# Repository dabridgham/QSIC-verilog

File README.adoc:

= QSIC - QBUS Storage and I/O Card

The QSIC is a QBUS card with an FPGA and SD cards that emulates the old DEC disk
controllers and drives.  A companion
http://github.com/dabridgham/Indicator-Panel[indicator panel] is also
available for those who want the blinkenlights.

This project has been split into separate repositories so that it
works better with git.  This repository primarily holds the Verilog
code that runs on the FPGAs.  It also holds the documentation and the
paper I wrote on bus arbitration.  Finally, just because there's no
more work being done on it, I've left the KiCad schematic for the
wire-wrapped prototype here as well.

So, directories you might care about are:

[horizontal]
board-wirewrap:: KiCad design for the wire-wrap prototype board
documentation:: Programming Manual for the QSIC/USIC
papers:: A paper on QBUS and Unibus arbitration
verilog:: The FPGA code to implement the QSIC

These directories, I'll probably make go away at some point but, for
now, I'll leave them be.

[horizontal]
board-prototype:: KiCad design for a prototype board with 8641 bus
		  transceivers (old idea)
board-qsic:: KiCad design for the QSIC hardware
board-smt:: KiCad design where I've been experimenting with discrete bus drivers
indicator-panel:: This directory is obsolete as the indicator panel has
		  been moved to its own project

Other QSIC-related repositories.

[horizontal]
https://github.com/dabridgham/QSIC[QSIC]:: The QSIC board
https://github.com/dabridgham/USIC[USIC]:: The USIC board
http://github.com/dabridgham/Indicator-Panel[Indicator Panel]:: Indicator Panel PCBs and graphics inlays
Software:: The software that runs on the embedded soft processor in
the QSIC/USIC (not yet started)

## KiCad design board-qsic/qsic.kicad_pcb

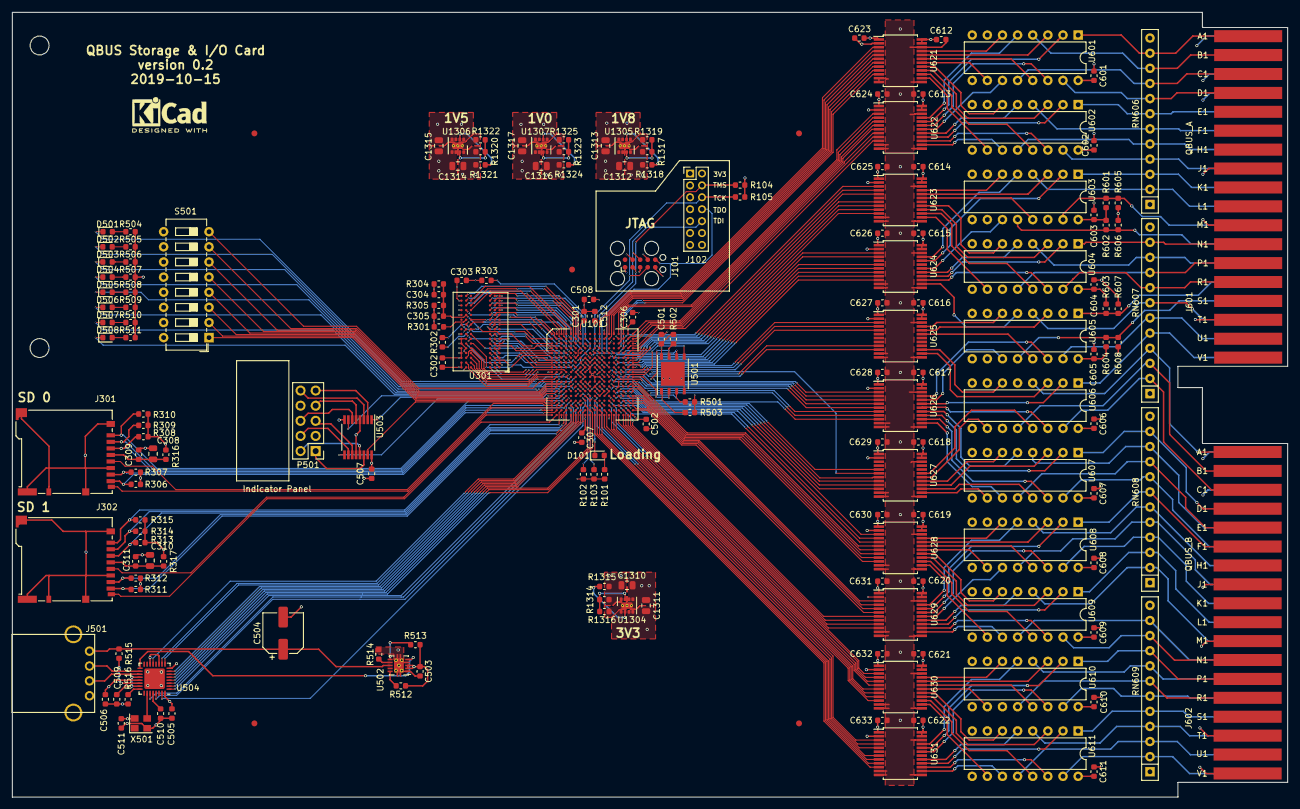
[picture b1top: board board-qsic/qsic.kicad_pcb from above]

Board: 4 copper layers, 214.1 x 131.7 mm, 183 parts (0 on the bottom side), 358 nets.

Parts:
C301, C306, C508, C512: 10µF; C_0603_1608Metric
C302, C303, C304, C305, C309, C311, C501, C503, C505, C506, C507, C601, C602, C603, C604, C605, C606, C607, C608, C609, C610, C611, C612, C613, C614, C615, C616, C617, C618, C619, C620, C621, C622, C623, C624, C625, C626, C627, C628, C629, C630, C631, C632, C633: 100nF; C_0603_1608Metric
C307, C502: 10uF; C_0603_1608Metric
C308, C310, C1310, C1312, C1314, C1316: 22µF; C_0805_2012Metric
C504: 150µF; CP_Elec_6.3x5.7
C509, C510: 1µF; C_0603_1608Metric
C511: 10nF; C_0603_1608Metric
C1311, C1313, C1315, C1317: 10µF; C_0805_2012Metric
D101, D501, D502, D503, D504, D505, D506, D507, D508: green; LED_0603_1608Metric
FID101, FID102, FID103, FID104, FID105: Fiducial; Fiducial_1mm_Mask2mm
J101: Conn_02x05_Odd_Even; Tag-Connect_TC2050-IDC-FP_2x05_P1.27mm_Vertical
J102: Conn_02x07_Odd_Even; PinHeader_2x07_P2.00mm_Vertical
J301: SD 0; microSD_HC_Hirose_DM3BT-DSF-PEJS
J302: SD 1; microSD_HC_Hirose_DM3BT-DSF-PEJS
J501: USB_A; USB-A-Amphenol-UE27
J601: QBUS_A; DEC_Edge_Fingers_single_height
J602: QBUS_B; DEC_Edge_Fingers_single_height
LOGO101: Logo_Open_Hardware_Small; KiCad-Logo2_5mm_SilkScreen
P501: Indicator Panel; Box_Header_2x05_P2.54mm
R101, R301, R504, R505, R506, R507, R508, R509, R510, R511: 240; R_0603_1608Metric
R102, R103, R501, R502: 4.7k; R_0603_1608Metric
R104, R105: 10k; R_0603_1608Metric
R302: 89; R_0603_1608Metric
R303: 47k; R_0603_1608Metric
R304, R305: 47 1%; R_0603_1608Metric
R306, R307, R308, R309, R310, R311, R312, R313, R314, R315: 50k; R_0603_1608Metric
R316, R317: 4.7; R_0603_1608Metric
R503: 2.4k; R_0603_1608Metric
R512, R513: 100k; R_0603_1608Metric
R514: 56.2k; R_0603_1608Metric
R515: 20k; R_0603_1608Metric
R516: 8.06k; R_0603_1608Metric
R601, R602, R603, R604: 330; R_0603_1608Metric
R605, R606, R607, R608: 680; R_0603_1608Metric
R1314: 511k; R_0603_1608Metric
R1315, R1318, R1321, R1324: 499k; R_0603_1608Metric
R1316, R1319, R1322, R1325: 162k; R_0603_1608Metric
R1317: 200k; R_0603_1608Metric
R1320: 143k; R_0603_1608Metric
R1323: 40.2; R_0603_1608Metric
RN606, RN607, RN608, RN609: 330/680; R_Array_SIP12
S501: Config; SW_DIP_SPSTx08_Slide_6.7x21.88mm_W7.62mm_P2.54mm_LowProfile
U101: XC7A75T-CSG324; BGA-324_15.0x15.0mm_Layout18x18_P0.8mm_Ball0.5mm_Pad0.4mm_N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
U301: IS43TR16128B; BGA-96_9.0x13.0mm_Layout2x3x16_P0.8mm
U501: MT25Q-mlq8; DFN-8-1EP_6x5mm_P1.27mm_EP4x4mm
U502: TPS2561; VSON-10-1EP_3x3mm_P0.5mm_EP1.65x2.4mm_ThermalVias
U503: MAX3033E; TSSOP-16_4.4x5mm_P0.65mm
U504: USB3340; QFN-32-1EP_5x5mm_P0.5mm_EP3.45x3.45mm
U601, U602, U603, U604, U605, U606, U607, U608, U609, U610, U611: DS8641-small; DIP-16_W7.62mm
U621, U622, U623, U624, U625, U626, U627, U628, U629, U630, U631: 74LVC8T245-small; SSOP-24_5.3x8.2mm_P0.65mm
U1304, U1305, U1306, U1307: TPS82085; Texas_SIL0008D_MicroSiP-8-1EP_2.8x3mm_P0.65mm_EP1.1x1.9mm_T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
X501: ASE-24.000MHz; Oscillator_SMD_Abracon_ASE-4Pin_3.2x2.5mm

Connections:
/1V0: C512.1, C1316.1, R1323.1, R1324.1, U101.F8, U101.F10, U101.G7, U101.G9, U101.G11, U101.H8, U101.J7, U101.J11, U101.K8, U101.L7, U101.L11, U101.M8, U101.M10, U101.N7, U101.N9, U101.N11, U1307.8
/1V5: C301.1, C302.1, C303.1, C304.1, C1314.1, R304.1, R1320.1, R1321.1, U101.A7, U101.C3, U101.D6, U101.F2, U101.G5, U101.J1, U301.A1, U301.A8, U301.B2, U301.C1, U301.C9, U301.D2, U301.D9, U301.E9, U301.F1, U301.G7, U301.H2, U301.H9, U301.K2, U301.K8, U301.N1, U301.N9, U301.R1, U301.R9, U1306.8
/1V8: C508.1, C1312.1, R1317.1, R1318.1, U101.B10, U101.F12, U101.H10, U101.H12, U101.K12, U101.M12, U1305.8
/3V3: C306.1, C307.1, C501.1, C502.1, C505.1, C506.1, C507.1, C511.1, C623.1, C624.1, C625.1, C626.1, C627.1, C628.1, C629.1, C630.1, C631.1, C632.1, C633.1, C1310.1, J101.1, J102.2, R101.1, R102.1, R103.1, R104.1, R105.1, R306.1, R307.1, R308.1, R309.1, R310.1, R311.1, R312.1, R313.1, R314.1, R315.1, R316.2, R317.2, R501.1, R502.1, R503.1, R504.1, R505.1, R506.1, R507.1, R508.1, R509.1, R510.1, R511.1, R1314.1, R1315.1, U101.A17, U101.C13, U101.D16, U101.G15, U101.H18, U101.K4, U101.K14, U101.L17, U101.N3, U101.N13, U101.P6, U101.P8, U101.P12, U101.P16, U101.R9, U101.T2, U101.T12, U101.U5, U101.U15, U101.V8, U101.V18, U501.8, U503.4, U503.12, U503.16, U504.8, U504.11, U504.14, U504.21, U504.32, U621.1, U622.1, U622.2, U623.1, U624.1, U624.2, U625.1, U626.1, U626.2, U627.1, U628.1, U629.1, U629.2, U630.1, U631.1, U631.2, U1304.8, X501.4
/5V0: C503.1, C601.1, C602.1, C603.1, C604.1, C605.1, C606.1, C607.1, C608.1, C609.1, C610.1, C611.1, C612.1, C613.1, C614.1, C615.1, C616.1, C617.1, C618.1, C619.1, C620.1, C621.1, C622.1, C1311.1, C1313.1, C1315.1, C1317.1, J601.A2, J601.D2, J602.A2, J602.V1, R512.1, R513.1, R601.1, R602.1, R603.1, R604.1, RN606.12, RN607.12, RN608.12, RN609.12, U502.2, U502.3, U601.16, U602.16, U603.16, U604.16, U605.16, U606.16, U607.16, U608.16, U609.16, U610.16, U611.16, U621.23, U621.24, U622.23, U622.24, U623.23, U623.24, U624.23, U624.24, U625.23, U625.24, U626.23, U626.24, U627.23, U627.24, U628.23, U628.24, U629.23, U629.24, U630.23, U630.24, U631.23, U631.24, U1304.1, U1304.3, U1304.4, U1305.1, U1305.3, U1305.4, U1306.1, U1306.3, U1306.4, U1307.1, U1307.3, U1307.4
/Memory/A0: U101.C5, U301.N3
/Memory/A1: U101.B6, U301.P7
/Memory/A2: U101.C7, U301.P3
/Memory/A3: U101.D5, U301.N2
/Memory/A4: U101.A3, U301.P8
/Memory/A5: U101.E7, U301.P2
/Memory/A6: U101.A4, U301.R8
/Memory/A7: U101.C6, U301.R2
/Memory/A8: U101.A6, U301.T8
/Memory/A9: U101.D8, U301.R3
/Memory/A10: U101.B2, U301.L7
/Memory/A11: U101.A5, U301.R7
/Memory/A12: U101.B3, U301.N7
/Memory/A13: U101.B7, U301.T3
/Memory/BA0: U101.E5, U301.M2
/Memory/BA1: U101.A1, U301.N8
/Memory/BA2: U101.E6, U301.M3
/Memory/CAS#: U101.D3, U301.K3
/Memory/CK: R302.2, U101.C4, U301.J7
/Memory/CK#: R302.1, U101.B4, U301.K7
/Memory/CKE: U101.B1, U301.K9
/Memory/DML: U101.G1, U301.E7
/Memory/DMU: U101.G6, U301.D3
/Memory/DQL0: U101.H1, U301.E3
/Memory/DQL1: U101.F1, U301.F7
/Memory/DQL2: U101.E2, U301.F2
/Memory/DQL3: U101.E1, U301.F8
/Memory/DQL4: U101.F4, U301.H3
/Memory/DQL5: U101.C1, U301.H8
/Memory/DQL6: U101.F3, U301.G2
/Memory/DQL7: U101.D2, U301.H7
/Memory/DQSL: U101.H2, U301.F3
/Memory/DQSL#: U101.G2, U301.G3
/Memory/DQSU: U101.J4, U301.C7
/Memory/DQSU#: U101.H4, U301.B7
/Memory/DQU0: U101.G4, U301.D7
/Memory/DQU1: U101.H5, U301.C3
/Memory/DQU2: U101.G3, U301.C8
/Memory/DQU3: U101.H6, U301.C2
/Memory/DQU4: U101.J2, U301.A7
/Memory/DQU5: U101.J3, U301.A2
/Memory/DQU6: U101.K1, U301.B8
/Memory/DQU7: U101.K2, U301.A3
/Memory/ODT: U101.F5, U301.K1
/Memory/RAS#: U101.E3, U301.J3
/Memory/RESET#: R303.1, U101.J5, U301.T2
/Memory/VREF15: C304.2, C305.1, R304.2, R305.1, U101.D7, U101.F6, U301.H1, U301.M8
/Memory/WE#: U101.D4, U301.L3
/QBUS & I/O/CCLK: U101.E9, U501.6
/QBUS & I/O/IPblank_N: P501.7, U503.5
/QBUS & I/O/IPblank_P: P501.6, U503.6
/QBUS & I/O/IPclk_N: P501.10, U503.3
/QBUS & I/O/IPclk_P: P501.9, U503.2
/QBUS & I/O/IPdata_N: P501.2, U503.13
/QBUS & I/O/IPdata_P: P501.1, U503.14
/QBUS & I/O/IPlatch_N: P501.5, U503.11
/QBUS & I/O/IPlatch_P: P501.4, U503.10
/QBUS & I/O/LED_0: D501.1, U101.K3
/QBUS & I/O/LED_1: D502.1, U101.K5
/QBUS & I/O/LED_2: D503.1, U101.K6
/QBUS & I/O/LED_3: D504.1, U101.L4
/QBUS & I/O/LED_4: D505.1, U101.L5
/QBUS & I/O/LED_5: D506.1, U101.N5
/QBUS & I/O/LED_6: D507.1, U101.M6
/QBUS & I/O/LED_7: D508.1, U101.M3
/QBUS & I/O/QBUS-int/BBS7: J601.P2, RN607.10, U604.4
/QBUS & I/O/QBUS-int/BDAL0: J601.U2, RN607.6, U605.15
/QBUS & I/O/QBUS-int/BDAL1: J601.V2, RN607.5, U606.1
/QBUS & I/O/QBUS-int/BDAL2: J602.E2, RN608.10, U607.4
/QBUS & I/O/QBUS-int/BDAL3: J602.F2, RN608.8, U607.15
/QBUS & I/O/QBUS-int/BDAL4: J602.H2, RN608.6, U608.4
/QBUS & I/O/QBUS-int/BDAL5: J602.J2, RN608.5, U608.12
/QBUS & I/O/QBUS-int/BDAL6: J602.K2, RN608.4, U608.15
/QBUS & I/O/QBUS-int/BDAL7: J602.L2, RN608.3, U609.1
/QBUS & I/O/QBUS-int/BDAL8: J602.M2, RN608.2, U609.4
/QBUS & I/O/QBUS-int/BDAL9: J602.N2, RN609.11, U609.12
/QBUS & I/O/QBUS-int/BDAL10: J602.P2, RN609.8, U610.4
/QBUS & I/O/QBUS-int/BDAL11: J602.R2, RN609.6, U610.15
/QBUS & I/O/QBUS-int/BDAL12: J602.S2, RN609.5, U611.1
/QBUS & I/O/QBUS-int/BDAL13: J602.T2, RN609.4, U611.4
/QBUS & I/O/QBUS-int/BDAL14: J602.U2, RN609.3, U611.12
/QBUS & I/O/QBUS-int/BDAL15: J602.V2, RN609.2, U611.15
/QBUS & I/O/QBUS-int/BDAL16: J601.C1, RN606.9, U601.12
/QBUS & I/O/QBUS-int/BDAL17: J601.D1, RN606.8, U601.15
/QBUS & I/O/QBUS-int/BDAL18: J602.C1, RN607.2, U606.15
/QBUS & I/O/QBUS-int/BDAL19: J602.D1, RN608.11, U607.1
/QBUS & I/O/QBUS-int/BDAL20: J602.E1, RN608.9, U607.12
/QBUS & I/O/QBUS-int/BDAL21: J602.F1, RN608.7, U608.1
/QBUS & I/O/QBUS-int/BDCOK: J602.A1, RN607.4, U606.4
/QBUS & I/O/QBUS-int/BDIN: J601.H2, RN606.5, U602.12
/QBUS & I/O/QBUS-int/BDMGI: J601.R2, R603.2, R607.1, U605.1
/QBUS & I/O/QBUS-int/BDMGO: J601.S2, R604.2, R608.1, U605.12
/QBUS & I/O/QBUS-int/BDMR: J601.N1, RN607.11, U604.1
/QBUS & I/O/QBUS-int/BDOUT: J601.E2, RN606.7, U602.1
/QBUS & I/O/QBUS-int/BEVNT: J602.R1, RN609.7, U610.12
/QBUS & I/O/QBUS-int/BHALT: J601.P1, RN607.9, U604.12
/QBUS & I/O/QBUS-int/BIAKI: J601.M2, R601.2, R605.1, U603.15
/QBUS & I/O/QBUS-int/BIAKO: J601.N2, R602.2, R606.1, U603.12
/QBUS & I/O/QBUS-int/BINIT: J601.T2, RN607.7, U605.4
/QBUS & I/O/QBUS-int/BIRQ4: J601.L2, RN606.2, U603.4
/QBUS & I/O/QBUS-int/BIRQ5: J601.A1, RN606.11, U601.1
/QBUS & I/O/QBUS-int/BIRQ6: J601.B1, RN606.10, U601.4
/QBUS & I/O/QBUS-int/BIRQ7: J602.P1, RN609.9, U610.1
/QBUS & I/O/QBUS-int/BPOK: J602.B1, RN607.3, U606.12
/QBUS & I/O/QBUS-int/BREF: J601.R1, RN607.8, U604.15
/QBUS & I/O/QBUS-int/BRPLY: J601.F2, RN606.6, U602.4
/QBUS & I/O/QBUS-int/BSACK: J602.N1, RN609.10, U609.15
/QBUS & I/O/QBUS-int/BSYNC: J601.J2, RN606.4, U602.15
/QBUS & I/O/QBUS-int/BWTBT: J601.K2, RN606.3, U603.1
/QBUS & I/O/RBS7: U101.E18, U623.7
/QBUS & I/O/RDAL0: U101.H16, U625.5
/QBUS & I/O/RDAL1: U101.J13, U625.10
/QBUS & I/O/RDAL2: U101.N14, U627.7
/QBUS & I/O/RDAL3: U101.P15, U627.9
/QBUS & I/O/RDAL4: U101.R16, U628.3
/QBUS & I/O/RDAL5: U101.M17, U628.6
/QBUS & I/O/RDAL6: U101.T16, U628.5
/QBUS & I/O/RDAL7: U101.N17, U628.8
/QBUS & I/O/RDAL8: U101.M18, U628.7
/QBUS & I/O/RDAL9: U101.P17, U628.10
/QBUS & I/O/RDAL10: U101.V16, U630.3
/QBUS & I/O/RDAL11: U101.T13, U630.5
/QBUS & I/O/RDAL12: U101.V14, U630.8
/QBUS & I/O/RDAL13: U101.U14, U630.7
/QBUS & I/O/RDAL14: U101.U12, U630.10
/QBUS & I/O/RDAL15: U101.U13, U630.9
/QBUS & I/O/RDAL16: U101.B13, U621.6
/QBUS & I/O/RDAL17: U101.A13, U621.5
/QBUS & I/O/RDAL18: U101.N15, U627.5
/QBUS & I/O/RDAL19: U101.P14, U627.8
/QBUS & I/O/RDAL20: U101.R15, U627.10
/QBUS & I/O/RDAL21: U101.R13, U628.4
/QBUS & I/O/RDCOK: U101.J15, U625.9
/QBUS & I/O/RDIN: U101.E15, U621.10
/QBUS & I/O/RDMGI: U101.J18, U625.4
/QBUS & I/O/RDMR: U101.F16, U623.8
/QBUS & I/O/RDOUT: U101.A15, U621.8
/QBUS & I/O/REVNT: U101.T14, U630.6
/QBUS & I/O/RHALT: U101.E16, U623.10
/QBUS & I/O/RIAKI: U101.E17, U623.5
/QBUS & I/O/RINIT: U101.J17, U625.3
/QBUS & I/O/RIRQ4: U101.B16, U623.3
/QBUS & I/O/RIRQ5: U101.B12, U621.4
/QBUS & I/O/RIRQ6: U101.A11, U621.3
/QBUS & I/O/RIRQ7: U101.V15, U630.4
/QBUS & I/O/RPOK: U101.H14, U627.6
/QBUS & I/O/RREF: U101.F18, U623.9
/QBUS & I/O/RRPLY: U101.A14, U621.7
/QBUS & I/O/RSACK: U101.P18, U628.9
/QBUS & I/O/RSYNC: U101.D15, U621.9
/QBUS & I/O/RWTBT: U101.C16, U623.4
/QBUS & I/O/SW_0: S501.8, U101.L1
/QBUS & I/O/SW_1: S501.7, U101.L3
/QBUS & I/O/SW_2: S501.6, U101.M1
/QBUS & I/O/SW_3: S501.5, U101.M2
/QBUS & I/O/SW_4: S501.4, U101.N1
/QBUS & I/O/SW_5: S501.3, U101.N2
/QBUS & I/O/SW_6: S501.2, U101.P2
/QBUS & I/O/SW_7: S501.1, U101.R1
/QBUS & I/O/TBS7: U101.G18, U624.7
/QBUS & I/O/TDAL0: U101.K13, U626.3
/QBUS & I/O/TDAL1: U101.J14, U626.5
/QBUS & I/O/TDAL2: U101.L18, U626.7
/QBUS & I/O/TDAL3: U101.N16, U626.9
/QBUS & I/O/TDAL4: U101.R18, U629.3
/QBUS & I/O/TDAL5: U101.U18, U629.6
/QBUS & I/O/TDAL6: U101.T18, U629.5
/QBUS & I/O/TDAL7: U101.U17, U629.8
/QBUS & I/O/TDAL8: U101.T15, U629.7
/QBUS & I/O/TDAL9: U101.U16, U629.10
/QBUS & I/O/TDAL10: U101.V12, U631.3
/QBUS & I/O/TDAL11: U101.R10, U631.5
/QBUS & I/O/TDAL12: U101.V11, U631.8
/QBUS & I/O/TDAL13: U101.U11, U631.7
/QBUS & I/O/TDAL14: U101.V10, U631.10
/QBUS & I/O/TDAL15: U101.T10, U631.9
/QBUS & I/O/TDAL16: U101.B17, U622.6
/QBUS & I/O/TDAL17: U101.A18, U622.5
/QBUS & I/O/TDAL18: U101.K15, U626.6
/QBUS & I/O/TDAL19: U101.M16, U626.8
/QBUS & I/O/TDAL20: U101.M13, U626.10
/QBUS & I/O/TDAL21: U101.R17, U629.4
/QBUS & I/O/TDIN: U101.D18, U622.10
/QBUS & I/O/TDMGO: U101.K16, U626.4
/QBUS & I/O/TDMR: U101.G14, U624.8
/QBUS & I/O/TDOUT: U101.C17, U622.8
/QBUS & I/O/TIAKO: U101.G17, U624.6
/QBUS & I/O/TINIT: U101.H17, U624.10
/QBUS & I/O/TIRQ4: U101.F14, U624.3
/QBUS & I/O/TIRQ5: U101.A16, U622.4
/QBUS & I/O/TIRQ6: U101.C15, U622.3
/QBUS & I/O/TIRQ7: U101.T11, U631.4
/QBUS & I/O/TREF: U101.G16, U624.9
/QBUS & I/O/TRPLY: U101.B18, U622.7
/QBUS & I/O/TSACK: U101.V17, U629.9
/QBUS & I/O/TSYNC: U101.D17, U622.9
/QBUS & I/O/TWTBT: U101.F13, U624.4
/QBUS & I/O/ip_blank: U101.M4, U503.7
/QBUS & I/O/ip_clk: U101.N4, U503.1
/QBUS & I/O/ip_data: U101.R2, U503.15
/QBUS & I/O/ip_latch: U101.P3, U503.9
/QBUS & I/O/sd0_clk: J301.5, U101.T1
/QBUS & I/O/sd0_cmd: J301.3, R308.2, U101.T4
/QBUS & I/O/sd0_dat0: J301.7, R307.2, U101.U1
/QBUS & I/O/sd0_dat1: J301.8, R306.2, U101.U2
/QBUS & I/O/sd0_dat2: J301.1, R310.2, U101.P4
/QBUS & I/O/sd0_dat3: J301.2, R309.2, U101.R3
/QBUS & I/O/sd0_det: J301.9, U101.T3
/QBUS & I/O/sd1_clk: J302.5, U101.V1
/QBUS & I/O/sd1_cmd: J302.3, R313.2, U101.R5
/QBUS & I/O/sd1_dat0: J302.7, R312.2, U101.R6
/QBUS & I/O/sd1_dat1: J302.8, R311.2, U101.V4
/QBUS & I/O/sd1_dat2: J302.1, R315.2, U101.U3
/QBUS & I/O/sd1_dat3: J302.2, R314.2, U101.U4
/QBUS & I/O/sd1_det: J302.9, U101.V2
/QBUS & I/O/usb0_clk60: U101.T5, U504.1
/QBUS & I/O/usb0_d0: U101.V9, U504.3
/QBUS & I/O/usb0_d1: U101.T8, U504.4
/QBUS & I/O/usb0_d2: U101.U8, U504.5
/QBUS & I/O/usb0_d3: U101.V7, U504.6
/QBUS & I/O/usb0_d4: U101.U7, U504.7
/QBUS & I/O/usb0_d5: U101.V6, U504.9
/QBUS & I/O/usb0_d6: U101.U6, U504.10
/QBUS & I/O/usb0_d7: U101.V5, U504.13
/QBUS & I/O/usb0_dir: U101.R8, U504.31
/QBUS & I/O/usb0_nxt: U101.U9, U504.2
/QBUS & I/O/usb0_resetb: U101.T6, U504.27
/QBUS & I/O/usb0_stp: U101.R7, U504.29
/TCK: J101.4, J102.6, R105.2, U101.E10
/TDI: J101.8, J102.10, U101.E11
/TDO: J101.6, J102.8, U101.E13
/TMS: J101.2, J102.4, R104.2, U101.E12
GND: C301.2, C302.2, C303.2, C305.2, C306.2, C307.2, C308.2, C309.2, C310.2, C311.2, C501.2, C502.2, C503.2, C504.2, C505.2, C506.2, C507.2, C508.2, C509.2, C510.2, C511.2, C512.2, C601.2, C602.2, C603.2, C604.2, C605.2, C606.2, C607.2, C608.2, C609.2, C610.2, C611.2, C612.2, C613.2, C614.2, C615.2, C616.2, C617.2, C618.2, C619.2, C620.2, C621.2, C622.2, C623.2, C624.2, C625.2, C626.2, C627.2, C628.2, C629.2, C630.2, C631.2, C632.2, C633.2, C1310.2, C1311.2, C1312.2, C1313.2, C1314.2, C1315.2, C1316.2, C1317.2, J101.3, J101.5, J101.7, J101.9, J102.1, J102.3, J102.5, J102.7, J102.9, J102.11, J102.13, J301.6, J301.10, J301.11, J302.6, J302.10, J302.11, J501.4, J501.5, J601.C2, J601.J1, J601.M1, J601.T1, J602.C2, J602.J1, J602.M1, J602.T1, P501.3, P501.8, R301.2, R303.2, R305.2, R514.2, R516.2, R605.2, R606.2, R607.2, R608.2, R1316.2, R1319.2, R1322.2, R1325.2, RN606.1, RN607.1, RN608.1, RN609.1, S501.9, S501.10, S501.11, S501.12, S501.13, S501.14, S501.15, S501.16, U101.A2, U101.A12, U101.B5, U101.B15, U101.C8, U101.C18, U101.D1, U101.D11, U101.E4, U101.E8, U101.E14, U101.F7, U101.F9, U101.F11, U101.F17, U101.G8, U101.G10, U101.G12, U101.H3, U101.H7, U101.H9, U101.H11, U101.H13, U101.J6, U101.J8, U101.J9, U101.J10, U101.J12, U101.J16, U101.K7, U101.K9, U101.K10, U101.K11, U101.L2, U101.L8, U101.L9, U101.L10, U101.L12, U101.L15, U101.M5, U101.M7, U101.M9, U101.M11, U101.M15, U101.N8, U101.N10, U101.N12, U101.N18, U101.P1, U101.P11, U101.P13, U101.R4, U101.R14, U101.T7, U101.T17, U101.U10, U101.V3, U101.V13, U301.A9, U301.B1, U301.B3, U301.B9, U301.D1, U301.D8, U301.E1, U301.E2, U301.E8, U301.F9, U301.G1, U301.G8, U301.G9, U301.J2, U301.J8, U301.L2, U301.M1, U301.M9, U301.P1, U301.P9, U301.T1, U301.T9, U501.4, U501.9, U502.1, U502.4, U502.11, U503.8, U504.33, U601.7, U601.8, U601.9, U602.7, U602.8, U602.9, U603.7, U603.8, U603.9, U603.14, U604.7, U604.8, U604.9, U604.11, U605.2, U605.7, U605.8, U605.9, U606.5, U606.7, U606.8, U606.9, U606.11, U607.7, U607.8, U607.9, U608.7, U608.8, U608.9, U609.7, U609.8, U609.9, U610.7, U610.8, U610.9, U610.11, U611.7, U611.8, U611.9, U621.2, U621.11, U621.12, U621.13, U621.22, U622.11, U622.12, U622.13, U622.22, U623.2, U623.11, U623.12, U623.13, U623.22, U624.11, U624.12, U624.13, U624.22, U625.2, U625.11, U625.12, U625.13, U625.22, U626.11, U626.12, U626.13, U626.22, U627.2, U627.11, U627.12, U627.13, U627.22, U628.2, U628.11, U628.12, U628.13, U628.22, U629.11, U629.12, U629.13, U629.22, U630.2, U630.11, U630.12, U630.13, U630.22, U631.11, U631.12, U631.13, U631.22, U1304.5, U1304.6, U1304.9, U1305.5, U1305.6, U1305.9, U1306.5, U1306.6, U1306.9, U1307.5, U1307.6, U1307.9, X501.2
unnamed: C308.1, C309.1, J301.4, R316.1
unnamed: C310.1, C311.1, J302.4, R317.1
unnamed: C504.1, J501.1, R515.2, U502.8
unnamed: C509.1, U504.20, U504.23
unnamed: C510.1, U504.28
unnamed: D101.1, U101.P10
unnamed: D101.2, R101.2
unnamed: D501.2, R504.2
unnamed: D502.2, R505.2
unnamed: D503.2, R506.2
unnamed: D504.2, R507.2
unnamed: D505.2, R508.2
unnamed: D506.2, R509.2
unnamed: D507.2, R510.2
unnamed: D508.2, R511.2
unnamed: J501.2, U504.19
unnamed: J501.3, U504.18
unnamed: R102.2, U101.P7
unnamed: R103.2, U101.P9
unnamed: R301.1, U301.L8
unnamed: R501.2, U101.L14, U501.3
unnamed: R502.2, U101.M14, U501.7
unnamed: R503.2, U101.L13, U501.1
unnamed: R512.2, U502.10
unnamed: R513.2, U502.6
unnamed: R514.1, U502.7
unnamed: R515.1, U504.22
unnamed: R516.1, U504.24
unnamed: R1314.2, R1316.1, U1304.7
unnamed: R1315.2, U1304.2
unnamed: R1317.2, R1319.1, U1305.7
unnamed: R1318.2, U1305.2
unnamed: R1320.2, R1322.1, U1306.7
unnamed: R1321.2, U1306.2
unnamed: R1323.2, R1325.1, U1307.7
unnamed: R1324.2, U1307.2
unnamed: U101.K17, U501.5
unnamed: U101.K18, U501.2
unnamed: U502.5, U504.17
unnamed: U504.26, X501.3
unnamed: U601.2, U622.20
unnamed: U601.3, U621.20
unnamed: U601.5, U622.21
unnamed: U601.6, U621.21
unnamed: U601.10, U621.18
unnamed: U601.11, U622.18
unnamed: U601.13, U621.19
unnamed: U601.14, U622.19
unnamed: U602.2, U622.16
unnamed: U602.3, U621.16
unnamed: U602.5, U622.17
unnamed: U602.6, U621.17
unnamed: U602.10, U621.14
unnamed: U602.11, U622.14
unnamed: U602.13, U621.15
unnamed: U602.14, U622.15
unnamed: U603.2, U624.20
unnamed: U603.3, U623.20
unnamed: U603.5, U624.21
unnamed: U603.6, U623.21
unnamed: U603.11, U624.18
unnamed: U603.13, U623.19
unnamed: U604.2, U624.16
unnamed: U604.3, U623.16
unnamed: U604.5, U624.17
unnamed: U604.6, U623.17
unnamed: U604.10, U623.14
unnamed: U604.13, U623.15
unnamed: U604.14, U624.15
unnamed: U605.3, U625.20
unnamed: U605.5, U624.14
unnamed: U605.6, U625.21
unnamed: U605.11, U626.20
unnamed: U605.13, U625.19
unnamed: U605.14, U626.21
unnamed: U606.2, U626.19
unnamed: U606.3, U625.14
unnamed: U606.6, U625.15
unnamed: U606.10, U627.18
unnamed: U606.13, U627.19
unnamed: U606.14, U626.18
unnamed: U607.2, U626.16
unnamed: U607.3, U627.16
unnamed: U607.5, U626.17
unnamed: U607.6, U627.17
unnamed: U607.10, U627.14
unnamed: U607.11, U626.14
unnamed: U607.13, U627.15
unnamed: U607.14, U626.15
unnamed: U608.2, U629.20
unnamed: U608.3, U628.20
unnamed: U608.5, U629.21
unnamed: U608.6, U628.21
unnamed: U608.10, U628.18
unnamed: U608.11, U629.18
unnamed: U608.13, U628.19
unnamed: U608.14, U629.19
unnamed: U609.2, U629.16
unnamed: U609.3, U628.16
unnamed: U609.5, U629.17
unnamed: U609.6, U628.17
unnamed: U609.10, U628.14
unnamed: U609.11, U629.14
unnamed: U609.13, U628.15
unnamed: U609.14, U629.15
unnamed: U610.2, U631.20
unnamed: U610.3, U630.20
unnamed: U610.5, U631.21
unnamed: U610.6, U630.21
unnamed: U610.10, U630.18
unnamed: U610.13, U630.19
unnamed: U610.14, U631.19
unnamed: U611.2, U631.16
unnamed: U611.3, U630.16
unnamed: U611.5, U631.17
unnamed: U611.6, U630.17
unnamed: U611.10, U630.14
unnamed: U611.11, U631.14
unnamed: U611.13, U630.15
unnamed: U611.14, U631.15

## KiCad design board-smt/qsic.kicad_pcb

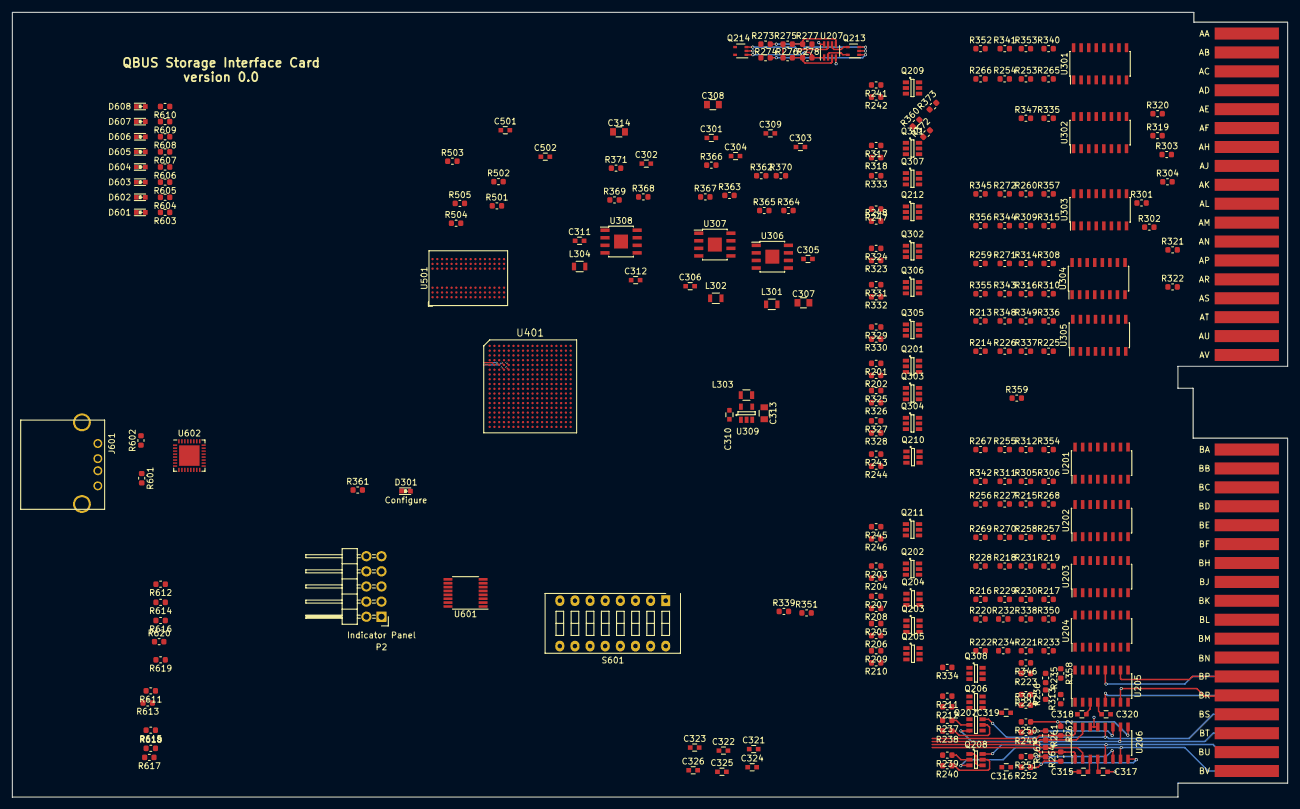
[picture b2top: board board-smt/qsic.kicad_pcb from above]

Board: 4 copper layers, 214.1 x 131.7 mm, 263 parts (0 on the bottom side), 270 nets.

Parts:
B101: QBUS; Qbus-double
C301, C302, C309, C310: 10uF; C_0603
C303, C304: 2.2nF; C_0603
C305, C306, C311, C312, C315, C316, C317, C318, C319, C320, C321, C322, C323, C324, C325, C326, C501, C502: 100nF; C_0603
C307, C308, C313, C314: 22uF; C_0805
D301: Configure; LED-0603
D601: LED 0; LED-0603
D602: LED 1; LED-0603
D603: LED 2; LED-0603
D604: LED 3; LED-0603
D605: LED 4; LED-0603
D606: LED 5; LED-0603
D607: LED 6; LED-0603
D608: LED 7; LED-0603
J601: USB_A
L301, L302: 4.7uH; R_0805
L303: 1.5uH; R_0805
L304: 2.2uH; R_0805
P2: Indicator Panel; Pin_Header_Angled_2x05
Q201, Q202, Q203, Q204, Q205, Q206, Q207, Q208, Q209, Q210, Q211, Q212, Q301, Q302, Q303, Q304, Q305, Q306, Q307, Q308: Dual_NMOS; SOT-23-6
Q213, Q214: DMN32; SOT-353_SC-70-5
R201, R202, R203, R204, R205, R206, R207, R208, R209, R210, R211, R212, R237, R238, R239, R240, R241, R242, R243, R244, R245, R246, R247, R248, R317, R318, R323, R324, R325, R326, R327, R328, R329, R330, R331, R332, R333, R334, R360, R603, R604, R605, R606, R607, R608, R609, R610: R; R_0603_1608Metric
R213, R214, R215, R216, R217, R218, R219, R220, R221, R222, R223, R224, R249, R250, R251, R252, R253, R254, R255, R256, R257, R258, R259, R260, R275, R276, R305, R306, R307, R308, R309, R310, R335, R336, R337, R338, R339, R340, R341, R342, R343, R344, R345, R346, R372: 20kΩ; R_0603_1608Metric
R225, R226, R227, R228, R229, R230, R231, R232, R233, R234, R235, R236, R261, R262, R263, R264, R265, R266, R267, R268, R269, R270, R271, R272, R277, R278, R311, R312, R313, R314, R315, R316, R347, R348, R349, R350, R351, R352, R353, R354, R355, R356, R357, R358, R373: 340kΩ; R_0603_1608Metric
R273, R274: 66; R_0603_1608Metric
R301, R303, R319, R321: 330; R_0603_1608Metric
R302, R304, R320, R322: 680; R_0603_1608Metric
R359: 5kΩ; R_0603_1608Metric
R361, R505: 240; R_0603_1608Metric
R362, R363: 7.5k; R_0603_1608Metric
R364: 31.1k; R_0603_1608Metric
R365, R366: 10k; R_0603_1608Metric
R367: 11.5k; R_0603_1608Metric
R368: 100k; R_0603_1608Metric
R369, R611, R612, R613, R614, R615, R616, R617, R619: 50k; R_0603_1608Metric
R370: 18.2k; R_0603_1608Metric
R371: 4.7k; R_0603_1608Metric
R501: 47k; R_0603_1608Metric
R502: 89; R_0603_1608Metric
R503, R504: 47; R_0603_1608Metric
R601, R602: 15k; R_0603_1608Metric
R618, R620: 270k; R_0603_1608Metric
S601: Config; SW_DIP_x8_Slide
U201, U202, U203, U204, U205, U206, U301, U302, U303, U304, U305: CMP401; SOIC-16_3.9x9.9mm_Pitch1.27mm
U207: MAX9107; SOT-23-8
U306, U307: AOZ3010PI; SOIC-8-1EP_3.9x4.9mm_Pitch1.27mm
U308: RT8288A; SOIC-8-1EP_3.9x4.9mm_Pitch1.27mm
U309: SC189; SOT-23-5
U401: XC7A75T-CSG324; CSG324
U501: IS43TR16128B; BGA-96_2x3x16_9.0x13.0mm_Pitch0.8mm
U601: MAX3033E; TSSOP-16_4.4x5mm_Pitch0.65mm
U602: USB3340; QFN-32-1EP_5x5mm_Pitch0.5mm

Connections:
+1V0: C314.1, L304.2, R371.1, U401.F8, U401.F10, U401.G7, U401.G9, U401.G11, U401.H8, U401.J7, U401.J11, U401.K8, U401.L7, U401.L11, U401.M8, U401.M10, U401.N7, U401.N9, U401.N11
+1V5: C308.1, C316.1, C319.1, C322.1, C325.1, C501.1, L302.2, R309.1, R310.1, R366.1, R503.1, U401.A7, U401.C3, U401.D6, U401.F2, U401.G5, U401.J1, U501.A1, U501.A8, U501.B2, U501.C1, U501.C9, U501.D2, U501.D9, U501.E9, U501.F1, U501.G7, U501.H2, U501.H9, U501.K2, U501.K8, U501.N1, U501.N9, U501.R1, U501.R9
+1V5_ref: R213.2, R214.2, R215.2, R216.2, R217.2, R218.2, R219.1, R220.2, R221.2, R222.2, R223.2, R224.2, R249.2, R250.2, R251.2, R252.2, R253.2, R254.2, R255.2, R256.2, R257.2, R258.2, R259.2, R260.2, R275.1, R276.1, R305.1, R306.1, R307.1, R308.1, R335.2, R336.2, R337.2, R338.2, R339.2, R340.2, R341.2, R342.2, R343.2, R344.2, R345.2, R346.2, R359.1, R372.2
+1V8: C313.1, L303.2, U309.4, U401.F12, U401.H12, U401.K12, U401.M12
+3V3: C307.1, C315.1, C318.1, C321.1, C324.1, D301.2, L301.2, R364.1, R603.1, R604.1, R605.1, R606.1, R607.1, R608.1, R609.1, R610.1, R611.1, R612.1, R613.1, R614.1, R615.1, R616.1, R617.1, R619.1, U201.3, U202.3, U203.3, U204.3, U205.3, U206.3, U301.3, U302.3, U303.3, U304.3, U305.3, U401.A17, U401.B10, U401.C13, U401.D16, U401.G15, U401.H18, U401.K4, U401.K14, U401.L17, U401.N3, U401.N13, U401.P6, U401.P8, U401.P16, U401.R9, U401.T2, U401.T12, U401.U5, U401.U15, U401.V8, U401.V18, U601.4, U601.12
+5V: B101.AA2, B101.BA2, B101.BV1, C301.2, C302.2, C309.2, C310.2, C317.1, C320.1, C323.1, C326.1, R301.1, R303.1, R319.1, R321.1, R368.2, U201.4, U202.4, U203.4, U204.4, U205.4, U206.4, U207.8, U301.4, U302.4, U303.4, U304.4, U305.4, U306.2, U306.6, U307.2, U307.6, U308.1, U309.1, U309.3
+12V: B101.AD2, B101.BD2
/Address/Data/BBS7: B101.AP2, Q212.6, U304.10
/Address/Data/BWTBT: B101.AK2, Q212.3, U303.12
/Address/Data/RDAL0: R225.2, U305.2
/Address/Data/RDAL1: R226.2, U305.1
/Address/Data/RDAL2: R227.2, U202.16
/Address/Data/RDAL3: R228.2, U203.15
/Address/Data/RDAL4: R229.2, U203.2
/Address/Data/RDAL5: R230.2, U203.1
/Address/Data/RDAL6: R231.2, U203.16
/Address/Data/RDAL7: R232.2, U204.15
/Address/Data/RDAL8: R233.2, U204.2
/Address/Data/RDAL9: R234.2, U204.1
/Address/Data/RDAL11: R236.2, U205.2
/Address/Data/RDAL12: R261.2, U206.15
/Address/Data/RDAL13: R262.1, U206.16
/Address/Data/RDAL14: R263.2, U206.2
/Address/Data/RDAL15: R264.2, U206.1
/Address/Data/RDAL16: R265.2, U301.2
/Address/Data/RDAL17: R266.2, U301.1
/Address/Data/RDAL18: R267.2, U201.16
/Address/Data/RDAL19: R268.2, U202.15
/Address/Data/RDAL20: R269.2, U202.2
/Address/Data/RDAL21: R270.2, U202.1
/BDAL0: B101.AU2, Q201.6, U305.5
/BDAL1: B101.AV2, Q201.3, U305.7
/BDAL2: B101.BE2, Q202.6, U202.10
/BDAL3: B101.BF2, Q202.3, U203.12
/BDAL4: B101.BH2, Q203.6, U203.5
/BDAL5: B101.BJ2, Q203.3, U203.7
/BDAL6: B101.BK2, Q204.6, U203.10
/BDAL7: B101.BL2, Q204.3, U204.12
/BDAL8: B101.BM2, Q205.6, U204.5
/BDAL9: B101.BN2, Q205.3, U204.7
/BDAL10: B101.BP2, Q206.6, U205.12
/BDAL11: B101.BR2, Q206.3, U205.5
/BDAL12: B101.BS2, Q207.6, U206.12
/BDAL13: B101.BT2, Q207.3, U206.10
/BDAL14: B101.BU2, Q208.6, U206.5
/BDAL15: B101.BV2, Q208.3, U206.7
/BDAL16: B101.AC1, Q209.6, U301.5
/BDAL17: B101.AD1, Q209.3, U301.7
/BDAL18: B101.BC1, Q210.6, U201.10
/BDAL19: B101.BD1, Q210.3, U202.12
/BDAL20: B101.BE1, Q211.6, U202.5
/BDAL21: B101.BF1, Q211.3, U202.7
/Bus Control/BDCOK: B101.BA1, U201.7
/Bus Control/BDIN: B101.AH2, Q302.3, U305.10
/Bus Control/BDMGI: B101.AR2, R303.2, R304.1, U304.7
/Bus Control/BDMGO: B101.AS2, Q301.3, R321.2, R322.1
/Bus Control/BDMR: B101.AN1, Q305.6, U301.12
/Bus Control/BDOUT: B101.AE2, Q303.6, U305.12
/Bus Control/BEVNT: B101.BR1, U205.7
/Bus Control/BHALT: B101.AP1, U304.12
/Bus Control/BIAKI: B101.AM2, R301.2, R302.1, U303.7
/Bus Control/BIAKO: B101.AN2, Q301.6, R319.2, R320.1
/Bus Control/BINIT: B101.AT2, Q304.3, U301.10
/Bus Control/BIRQ4: B101.AL2, Q306.6, U304.5
/Bus Control/BIRQ5: B101.AA1, Q213.4, Q306.3, U207.6, U303.5
/Bus Control/BIRQ6: B101.AB1, Q213.5, Q307.6, U207.2, U303.10
/Bus Control/BIRQ7: B101.BP1, Q307.3, Q308.6, U205.10
/Bus Control/BPOK: B101.BB1, U201.5
/Bus Control/BREF: B101.AR1, Q304.6, U302.5
/Bus Control/BRPLY: B101.AF2, Q303.3, U204.10
/Bus Control/BSACK: B101.BN1, Q305.3, U201.12
/Bus Control/BSYNC: B101.AJ2, Q302.6, U302.10
/I/O/IPblank_N: P2.7, U601.13
/I/O/IPblank_P: P2.6, U601.14
/I/O/IPclk_N: P2.10, U601.3
/I/O/IPclk_P: P2.9, U601.2
/I/O/IPdata_N: P2.2, U601.5
/I/O/IPdata_P: P2.1, U601.6
/I/O/IPlatch_N: P2.5, U601.11
/I/O/IPlatch_P: P2.4, U601.10
/I/O/USB_D+: J601.3, R602.1
/I/O/USB_D-: J601.2, R601.1
/Memory/A0: U401.C5, U501.N3
/Memory/A1: U401.B6, U501.P7
/Memory/A2: U401.C7, U501.P3
/Memory/A3: U401.D5, U501.N2
/Memory/A4: U401.A3, U501.P8
/Memory/A5: U401.E7, U501.P2
/Memory/A6: U401.A4, U501.R8
/Memory/A7: U401.C6, U501.R2
/Memory/A8: U401.A6, U501.T8
/Memory/A9: U401.D8, U501.R3
/Memory/A10: U401.B2, U501.L7
/Memory/A11: U401.A5, U501.R7
/Memory/A12: U401.B3, U501.N7
/Memory/A13: U401.B7, U501.T3
/Memory/BA0: U401.E5, U501.M2
/Memory/BA1: U401.A1, U501.N8
/Memory/BA2: U401.E6, U501.M3
/Memory/CAS#: U401.D3, U501.K3
/Memory/CK: R502.2, U401.C4, U501.J7
/Memory/CK#: R502.1, U401.B4, U501.K7
/Memory/CKE: U401.B1, U501.K9
/Memory/DML: U401.G1, U501.E7
/Memory/DMU: U401.G6, U501.D3
/Memory/DQL0: U401.H1, U501.E3
/Memory/DQL1: U401.F1, U501.F7
/Memory/DQL2: U401.E2, U501.F2
/Memory/DQL3: U401.E1, U501.F8
/Memory/DQL4: U401.F4, U501.H3
/Memory/DQL5: U401.C1, U501.H8
/Memory/DQL6: U401.F3, U501.G2
/Memory/DQL7: U401.D2, U501.H7
/Memory/DQSL: U401.H2, U501.F3
/Memory/DQSL#: U401.G2, U501.G3
/Memory/DQSU: U401.J4, U501.C7
/Memory/DQSU#: U401.H4, U501.B7
/Memory/DQU0: U401.G4, U501.D7
/Memory/DQU1: U401.H5, U501.C3
/Memory/DQU2: U401.G3, U501.C8
/Memory/DQU3: U401.H6, U501.C2
/Memory/DQU4: U401.J2, U501.A7
/Memory/DQU5: U401.J3, U501.A2
/Memory/DQU6: U401.K1, U501.B8
/Memory/DQU7: U401.K2, U501.A3
/Memory/ODT: U401.F5, U501.K1
/Memory/RAS#: U401.E3, U501.J3
/Memory/RESET#: R501.1, U401.J5, U501.T2
/Memory/VREF15: C501.2, C502.1, R503.2, R504.1, U401.D7, U401.F6, U501.H1, U501.M8
/Memory/WE#: U401.D4, U501.L3
/RBS7: R271.2, U304.16
/RDCOK: R312.1, U201.1
/RDIN: R348.2, U305.16
/RDMGI: R316.1, U304.1
/RDMR: R353.2, U301.15
/RDOUT: R349.2, U305.15
/REVNT: R313.1, U205.1
/RHALT: R314.1, U304.15
/RIAKI: R315.1, U303.1
/RINIT: R352.2, U301.16
/RIRQ4: R355.1, U304.2
/RIRQ5: Q214.4, R356.1, U303.2
/RIRQ6: Q214.5, R357.1, U303.16
/RIRQ7: R358.1, R373.1, U205.16
/RPOK: R311.1, U201.2
/RREF: R351.2, U302.2
/RRPLY: R350.2, U204.16
/RSACK: R354.2, U201.15
/RSYNC: R347.2, U302.16
/RWTBT: R272.2, U303.15
/TIRQ5: R273.2, R332.2
/TIRQ6: R274.2, R333.2
/TIRQ7: R334.2, R360.2
GND: B101.AC2, B101.AJ1, B101.AM1, B101.AT1, B101.BC2, B101.BJ1, B101.BT1, C301.1, C302.1, C303.2, C304.2, C305.2, C306.2, C307.2, C308.2, C309.1, C310.1, C312.2, C313.2, C314.2, C315.2, C316.2, C317.2, C318.2, C319.2, C320.2, C321.2, C322.2, C323.2, C324.2, C325.2, C326.2, C502.2, J601.4, J601.5, P2.3, P2.8, Q201.1, Q201.4, Q202.1, Q202.4, Q203.1, Q203.4, Q204.1, Q204.4, Q205.1, Q205.4, Q206.1, Q206.4, Q207.1, Q207.4, Q208.1, Q208.4, Q209.1, Q209.4, Q210.1, Q210.4, Q211.1, Q211.4, Q212.1, Q212.4, Q213.2, Q214.2, Q301.1, Q301.4, Q302.1, Q302.4, Q303.1, Q303.4, Q304.1, Q304.4, Q305.1, Q305.4, Q306.1, Q306.4, Q307.1, Q307.4, Q308.1, R302.2, R304.2, R320.2, R322.2, R359.2, R365.2, R367.2, R370.2, R501.2, R504.2, R505.2, R601.2, R602.2, R618.2, R620.2, S601.9, S601.10, S601.11, S601.12, S601.13, S601.14, S601.15, S601.16, U201.13, U201.14, U202.13, U202.14, U203.13, U203.14, U204.13, U204.14, U205.13, U205.14, U206.13, U206.14, U207.4, U301.13, U301.14, U302.13, U302.14, U303.13, U303.14, U304.13, U304.14, U305.13, U305.14, U306.1, U306.3, U307.1, U307.3, U308.8, U308.9, U309.2, U401.A2, U401.A12, U401.B5, U401.B15, U401.C8, U401.C18, U401.D1, U401.D11, U401.E4, U401.E14, U401.F7, U401.F9, U401.F11, U401.F17, U401.G8, U401.G10, U401.G12, U401.H3, U401.H7, U401.H9, U401.H11, U401.H13, U401.J6, U401.J8, U401.J9, U401.J12, U401.J16, U401.K7, U401.K10, U401.K11, U401.L2, U401.L8, U401.L12, U401.M5, U401.M7, U401.M9, U401.M11, U401.M15, U401.N8, U401.N10, U401.N12, U401.N18, U401.P1, U401.R4, U401.R14, U401.T7, U401.T17, U401.U10, U401.V3, U401.V13, U501.A9, U501.B1, U501.B3, U501.B9, U501.D1, U501.D8, U501.E1, U501.E2, U501.E8, U501.F9, U501.G1, U501.G8, U501.G9, U501.J2, U501.J8, U501.M1, U501.M9, U501.P1, U501.P9, U501.T1, U501.T9
unnamed: C303.1, R362.2
unnamed: C304.1, R363.2
unnamed: C305.1, U306.7
unnamed: C306.1, U307.7
unnamed: C311.1, U308.4
unnamed: C311.2, L304.1, U308.2, U308.3
unnamed: C312.1, U308.7
unnamed: D301.1, R361.1
unnamed: D601.2, R603.2
unnamed: D602.2, R604.2
unnamed: D603.2, R605.2
unnamed: D604.2, R606.2
unnamed: D605.2, R607.2
unnamed: D606.2, R608.2
unnamed: D607.2, R609.2
unnamed: D608.2, R610.2
unnamed: L301.1, U306.8, U306.9
unnamed: L302.1, U307.8, U307.9
unnamed: L303.1, U309.5
unnamed: Q201.2, R201.1
unnamed: Q201.5, R202.2
unnamed: Q202.2, R203.1
unnamed: Q202.5, R204.1
unnamed: Q203.2, R205.1
unnamed: Q203.5, R206.1
unnamed: Q204.2, R207.1
unnamed: Q204.5, R208.1
unnamed: Q205.2, R209.1
unnamed: Q205.5, R210.1
unnamed: Q206.2, R211.1
unnamed: Q206.5, R212.1
unnamed: Q207.2, R237.1
unnamed: Q207.5, R238.1
unnamed: Q208.2, R239.1
unnamed: Q208.5, R240.1
unnamed: Q209.2, R241.1
unnamed: Q209.5, R242.1
unnamed: Q210.2, R243.1
unnamed: Q210.5, R244.1
unnamed: Q211.2, R245.1
unnamed: Q211.5, R246.1
unnamed: Q212.2, R247.1
unnamed: Q212.5, R248.1
unnamed: Q213.1, R274.1
unnamed: Q213.3, R273.1
unnamed: Q214.1, R278.1, U207.1
unnamed: Q214.3, R277.1, U207.7
unnamed: Q301.2, R317.1
unnamed: Q301.5, R318.1
unnamed: Q302.2, R323.1
unnamed: Q302.5, R324.1
unnamed: Q303.2, R325.1
unnamed: Q303.5, R326.1
unnamed: Q304.2, R327.1
unnamed: Q304.5, R328.1
unnamed: Q305.2, R329.1
unnamed: Q305.5, R330.1
unnamed: Q306.2, R331.1
unnamed: Q306.5, R332.1
unnamed: Q307.2, R333.1
unnamed: Q307.5, R360.1
unnamed: Q308.2, R334.1
unnamed: R213.1, R225.1, U305.6
unnamed: R214.1, R226.1, U305.8
unnamed: R215.1, R227.1, U202.9
unnamed: R216.1, R228.1, U203.11
unnamed: R217.1, R229.1, U203.6
unnamed: R218.1, R230.1, U203.8
unnamed: R219.2, R231.1, U203.9
unnamed: R220.1, R232.1, U204.11
unnamed: R221.1, R233.1, U204.6
unnamed: R222.1, R234.1, U204.8
unnamed: R223.1, R235.1, U205.11
unnamed: R224.1, R236.1, U205.6
unnamed: R249.1, R261.1, U206.11
unnamed: R250.1, R262.2, U206.9
unnamed: R251.1, R263.1, U206.6
unnamed: R252.1, R264.1, U206.8
unnamed: R253.1, R265.1, U301.6
unnamed: R254.1, R266.1, U301.8
unnamed: R255.1, R267.1, U201.9
unnamed: R256.1, R268.1, U202.11
unnamed: R257.1, R269.1, U202.6
unnamed: R258.1, R270.1, U202.8
unnamed: R259.1, R271.1, U304.9
unnamed: R260.1, R272.1, U303.11
unnamed: R275.2, R277.2, U207.5
unnamed: R276.2, R278.2, U207.3
unnamed: R305.2, R311.2, U201.6
unnamed: R306.2, R312.2, U201.8
unnamed: R307.2, R313.2, U205.8
unnamed: R308.2, R314.2, U304.11
unnamed: R309.2, R315.2, U303.8
unnamed: R310.2, R316.2, U304.8
unnamed: R335.1, R347.1, U302.9
unnamed: R336.1, R348.1, U305.9
unnamed: R337.1, R349.1, U305.11
unnamed: R338.1, R350.1, U204.9
unnamed: R339.1, R351.1, U302.6
unnamed: R340.1, R352.1, U301.9
unnamed: R341.1, R353.1, U301.11
unnamed: R342.1, R354.1, U201.11
unnamed: R343.1, R355.2, U304.6
unnamed: R344.1, R356.2, U303.6
unnamed: R345.1, R357.2, U303.9
unnamed: R346.1, R358.2, U205.9
unnamed: R361.2, U401.P10
unnamed: R362.1, U306.5
unnamed: R363.1, U307.5
unnamed: R364.2, R365.1, U306.4
unnamed: R366.2, R367.1, U307.4
unnamed: R368.1, U308.5
unnamed: R369.1, R370.1, R371.2
unnamed: R369.2, U308.6
unnamed: R372.1, R373.2
unnamed: R505.1, U501.L8
